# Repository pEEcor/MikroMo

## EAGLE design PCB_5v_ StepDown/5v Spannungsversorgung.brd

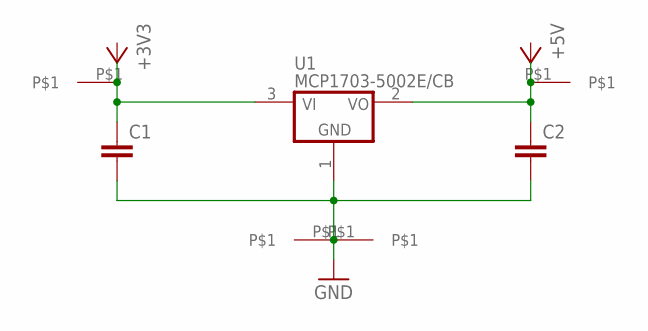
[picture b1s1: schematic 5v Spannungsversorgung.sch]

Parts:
C1, C2: C-EUC0603K; C0603K
U1: MCP1703-5002E/CB; SOT23A_MICROCHIP_CB
U$1, U$2, U$3, U$4: PAD

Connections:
GND: C1.2, C2.2, U1.1 (GND), U$2.P$1, U$4.P$1
unnamed: C1.1, U1.3 (VI), U$3.P$1
unnamed: C2.1, U1.2 (VO), U$1.P$1

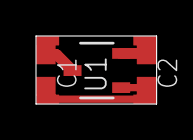
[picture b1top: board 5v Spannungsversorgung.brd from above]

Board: 2 copper layers, 6.7 x 3.8 mm, 7 parts (0 on the bottom side), 3 nets.

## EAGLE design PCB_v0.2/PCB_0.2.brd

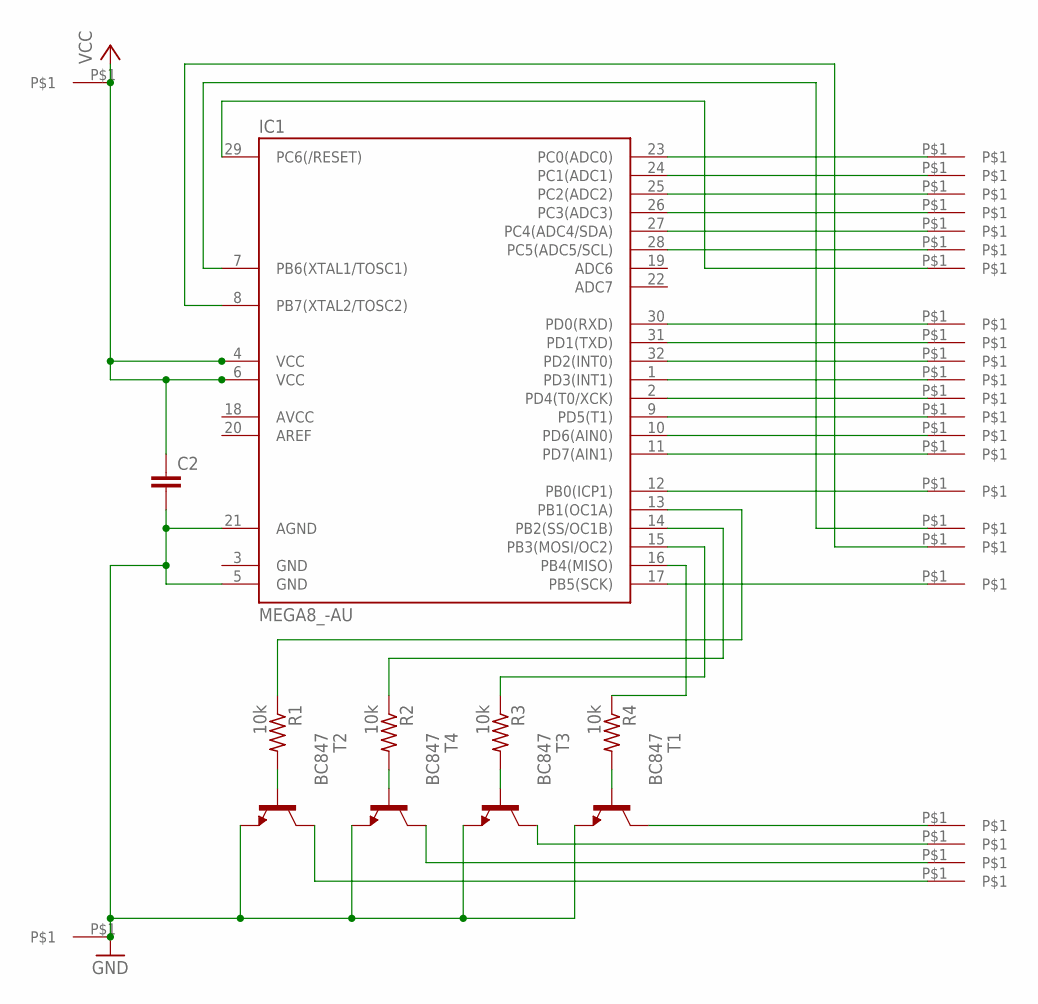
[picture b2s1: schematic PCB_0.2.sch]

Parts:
C2: C-EUC0603K; C0603K
IC1: MEGA8_-AU; TQFP32-08
PC0, PC1, PC2, PC3, PC4, PC5, PC6: Fahrkanal; PAD
R1, R2, R3, R4: 10k; R0402
T1, T2, T3, T4: BC847; SOT23
U$1, U$2, U$3, U$4, U$5, U$6, U$7, U$8, U$9, U$10, U$11, U$12, U$14, U$15, U$16, U$17, U$18, U$19: PAD

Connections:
GND: C2.2, IC1.3 (GND), IC1.5 (GND), IC1.21 (AGND), PC5.P$1, T1.2 (E), T2.2 (E), T3.2 (E), T4.2 (E)
unnamed: PC1.P$1, T1.3 (C)
unnamed: PC2.P$1, T3.3 (C)
unnamed: PC3.P$1, T4.3 (C)
unnamed: PC4.P$1, T2.3 (C)
unnamed: IC1.16 (PB4(MISO)), R4.1
unnamed: IC1.15 (PB3(MOSI/OC2)), R3.1
unnamed: IC1.14 (PB2(SS/OC1B)), R2.1
unnamed: IC1.13 (PB1(OC1A)), R1.1
unnamed: IC1.17 (PB5(SCK)), U$19.P$1
unnamed: IC1.23 (PC0(ADC0)), PC0.P$1
unnamed: IC1.24 (PC1(ADC1)), U$2.P$1
unnamed: IC1.25 (PC2(ADC2)), U$3.P$1
unnamed: IC1.26 (PC3(ADC3)), U$4.P$1
unnamed: IC1.27 (PC4(ADC4/SDA)), U$5.P$1
unnamed: IC1.28 (PC5(ADC5/SCL)), U$6.P$1
unnamed: IC1.29 (PC6(/RESET)), U$7.P$1
unnamed: IC1.30 (PD0(RXD)), U$8.P$1
unnamed: IC1.31 (PD1(TXD)), U$9.P$1
unnamed: IC1.32 (PD2(INT0)), U$10.P$1
unnamed: IC1.1 (PD3(INT1)), U$11.P$1
unnamed: IC1.2 (PD4(T0/XCK)), U$12.P$1
unnamed: IC1.10 (PD6(AIN0)), U$14.P$1
unnamed: IC1.9 (PD5(T1)), U$1.P$1
unnamed: IC1.11 (PD7(AIN1)), U$15.P$1
unnamed: IC1.12 (PB0(ICP1)), U$16.P$1
unnamed: R1.2, T2.1 (B)
unnamed: IC1.7 (PB6(XTAL1/TOSC1)), U$17.P$1
unnamed: IC1.8 (PB7(XTAL2/TOSC2)), U$18.P$1
unnamed: R3.2, T3.1 (B)
unnamed: R2.2, T4.1 (B)
unnamed: R4.2, T1.1 (B)
VCC: C2.1, IC1.4 (VCC), IC1.6 (VCC), PC6.P$1

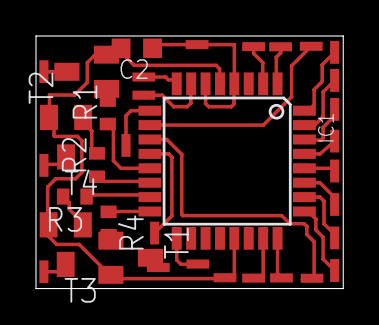
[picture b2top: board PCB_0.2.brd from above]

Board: 2 copper layers, 17.1 x 14.0 mm, 35 parts (0 on the bottom side), 33 nets.

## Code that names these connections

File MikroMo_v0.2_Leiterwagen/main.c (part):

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* Datum        : 16.09.14                                                      *
* Entwickler   : pEEcor                                                        *
*                                                                              *
* Funktion     : - liest SumPPM (high) an ICP1 (PB1) von Deltang Empfänger ein *
*                - splited die 7 Kanaele in 14 auf mit Kanal 5 als Umschalter  *
*                - gibt 9 Servoleitungen aus: - PC0 -> Fahren                  *
*                                             - PC1 -> Lenken                  *
*                                             - PC2 -> Stuetzen horizontal     *
*                                             - PC3 -> Stuetzen vertikal links *
*                                             - PC4 -> Stuetzen vertikal rechts*
*                                             - PC5 -> Leiter heben & senken   *
*                                             - PD6 -> Leiter drehen           *
*                                             - PD7 -> Leiter aus & -einfahren *
*                                             - PD5 -> Impuls fuer Horntiny    *
*                - gibt Lichtfunktionen aus:  - PB1 -> Abblendlicht            *
*                                             - PB2 -> Nebellicht              *
*                                             - PB3 -> Blinker links           *
*                                             - PB4 -> Blinker rechts          *
*                                             - PB5 -> BlinkerStuetzen links   *
*                                             - PB6 -> BlinkerStuetzen rechts  *
*                                             - PB7 -> Flutlicht               *
*                                             - PD0 -> Doppelblitzer 1         *
*                                             - PD4 -> Doppelblitzer 2         *
*                                                                              *
*******************************************************************************/

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                                 188, 188, 188, 188, 188, 188, 188};

// Servoausgaenge
uint8_t ServoPuls[9] = {1<<PC0, 1<<PC1, 1<<PC2, 1<<PC3, 1<<PC4, 1<<PC5, 1<<PD6, 1<<PD7, 1<<PD5};
volatile uint8_t ServoValue[9] = {188, 188, 188, 188, 188, 188, 188, 188, 188};

// Vergleichssekunden fuer MomoryFunktionserfassung
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    TIMSK |= (1<<TICIE1) | (1<<OCIE1A) | (1<<OCIE1B);           // Input Capture Interrupt / Compare Match A Interrupt / Compare Match B Interrupt
    OCR1A  = 40;                                                // Kanalwerte in funktionsarry speichern / funktionen ServoValue zuweisen
    OCR1B  = 50;                                                // memoryFunktionsabtastung abfragen
    TCCR1B |= (1<<CS11) | (1<<CS10) | (1<<ICNC1) | (1<<ICES1);  // Timer1: Prescaler 8 / Noise Cancelation / Input Capture Edge (high) PB1 (ICP1)
}


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void InitServo()
{
  // Die Servoleitungen auf Ausgang stellen
    DDRC |= (1<<PC0) | (1<<PC1) | (1<<PC2) | (1<<PC3) | (1<<PC4) | (1<<PC5);
    DDRD |= (1<<PD6) | (1<<PD7) | (1<<PD5);

    // Timer auf CTC Modus konfigurieren
    OCR2 = ServoValue[0];
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void InitLicht()
{
    // Lichtleitungen auf Ausgang
    DDRB  |= (1<<PB1) | (1<<PB2) | (1<<PB3) | (1<<PB4) | (1<<PB5) | (1<<PB6) | (1<<PB7);
    PORTB |= (1<<PB1) | (1<<PB2) | (1<<PB3) | (1<<PB4) | (1<<PB5) | (1<<PB6) | (1<<PB7);
    DDRD  |= (1<<PD0) | (1<<PD4);
    PORTD |= (1<<PD0) | (1<<PD4);

    // Timer auf Overflow konfigurieren
    TIMSK |= (1<<TOIE0);                            // Overflow Interrupt
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
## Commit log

2014-09-21 :octocat: Added .gitattributes & .gitignore files
2014-09-21 main files added
2014-09-22 folders changed
2014-09-22 moved readme.txt
2014-09-23 test
2014-09-23 test 2
2014-09-23 PCB folder added
2014-09-24 PCB added
2014-09-24 Pad.lbr added to PCB
2014-09-25 PCB updated
2014-09-26 blubb
2014-11-17 Complete reup
    - couple of minor bugs fixed
    - PCB update
2015-11-22 folder changes
2016-04-26 cleaning up
